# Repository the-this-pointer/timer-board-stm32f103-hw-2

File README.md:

# Timer Board Design Files

This repository contains the KiCAD PCB design files for my <a href="https://github.com/the-this-pointer/timer-board-stm32f103" target="_blank">universal timer board</a>.

There are two PCBs for main board and a panel board to let user set the configuration.

Caution: The PCBs not tested yet!

Main board:

Panel board:

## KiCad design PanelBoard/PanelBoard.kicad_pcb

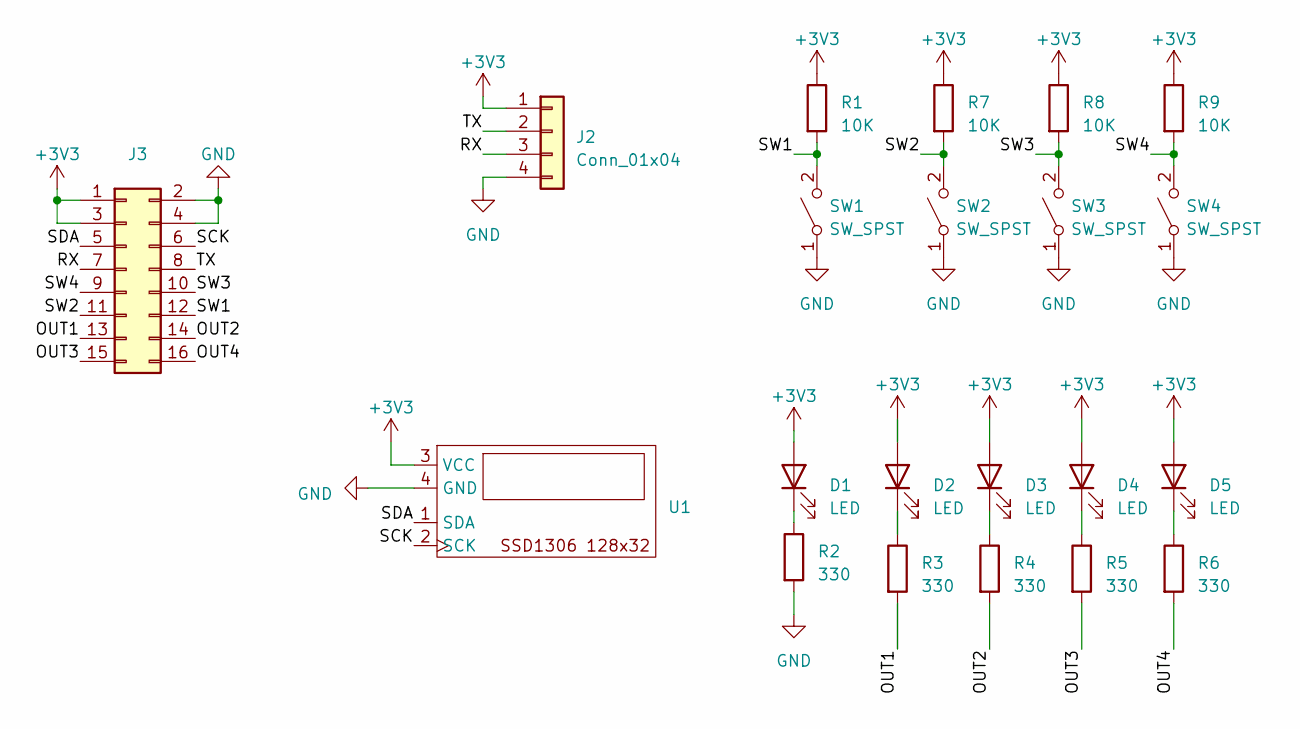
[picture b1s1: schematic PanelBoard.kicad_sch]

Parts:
D1, D2, D3, D4, D5: LED; LED_1206_3216Metric_Pad1.42x1.75mm_HandSolder
J2: Conn_01x04; PinHeader_1x04_P2.54mm_Vertical
J3: Conn_02x08_Odd_Even; PinHeader_2x08_P2.54mm_Horizontal
R1, R7, R8, R9: 10K; R_1206_3216Metric_Pad1.30x1.75mm_HandSolder
R2, R3, R4, R5, R6: 330; R_1206_3216Metric_Pad1.30x1.75mm_HandSolder
SW1, SW2, SW3, SW4: SW_SPST; SW_PUSH_6mm_H13mm
U1: OLED_SSD1306_128x32_0.91

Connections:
+3V3: D1.2 (A), D2.2 (A), D3.2 (A), D4.2 (A), D5.2 (A), J2.1, R1.1, R7.1, R8.1, R9.1, U1.3 (VCC); also elsewhere on the board
/OUT1: R3.2; also elsewhere on the board
/OUT2: R4.2; also elsewhere on the board
/OUT3: R5.2; also elsewhere on the board
/OUT4: R6.2; also elsewhere on the board
/RX: J2.3; also elsewhere on the board
/SCK: U1.2 (SCK); also elsewhere on the board
/SDA: U1.1 (SDA); also elsewhere on the board
/SW1: R1.2, SW1.2 (B); also elsewhere on the board
/SW2: R7.2, SW2.2 (B); also elsewhere on the board
/SW3: R8.2, SW3.2 (B); also elsewhere on the board
/SW4: R9.2, SW4.2 (B); also elsewhere on the board
/TX: J2.2; also elsewhere on the board
GND: J2.4, R2.2, SW1.1 (A), SW2.1 (A), SW3.1 (A), SW4.1 (A), U1.4 (GND); also elsewhere on the board
unnamed: D1.1 (K), R2.1
unnamed: D2.1 (K), R3.1
unnamed: D3.1 (K), R4.1
unnamed: D4.1 (K), R5.1
unnamed: D5.1 (K), R6.1

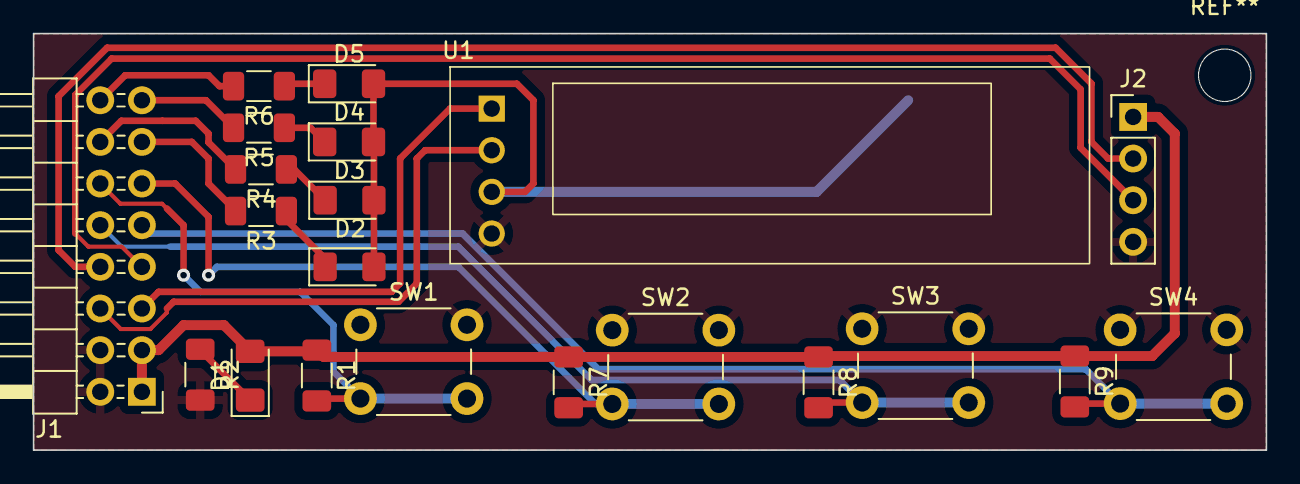
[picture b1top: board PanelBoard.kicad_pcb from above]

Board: 2 copper layers, 75.2 x 25.4 mm, 21 parts (0 on the bottom side), 19 nets.

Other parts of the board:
J1: Conn_02x08_Odd_Even; PinHeader_2x08_P2.54mm_Horizontal

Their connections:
+3V3: J1.1, J1.3; also elsewhere on the board
/OUT1: J1.13; also elsewhere on the board
/OUT2: J1.14; also elsewhere on the board
/OUT3: J1.15; also elsewhere on the board
/OUT4: J1.16; also elsewhere on the board
/RX: J1.7; also elsewhere on the board
/SCK: J1.6; also elsewhere on the board
/SDA: J1.5; also elsewhere on the board
/SW1: J1.12; also elsewhere on the board
/SW2: J1.11; also elsewhere on the board
/SW3: J1.10; also elsewhere on the board
/SW4: J1.9; also elsewhere on the board
/TX: J1.8; also elsewhere on the board
GND: J1.2, J1.4; also elsewhere on the board

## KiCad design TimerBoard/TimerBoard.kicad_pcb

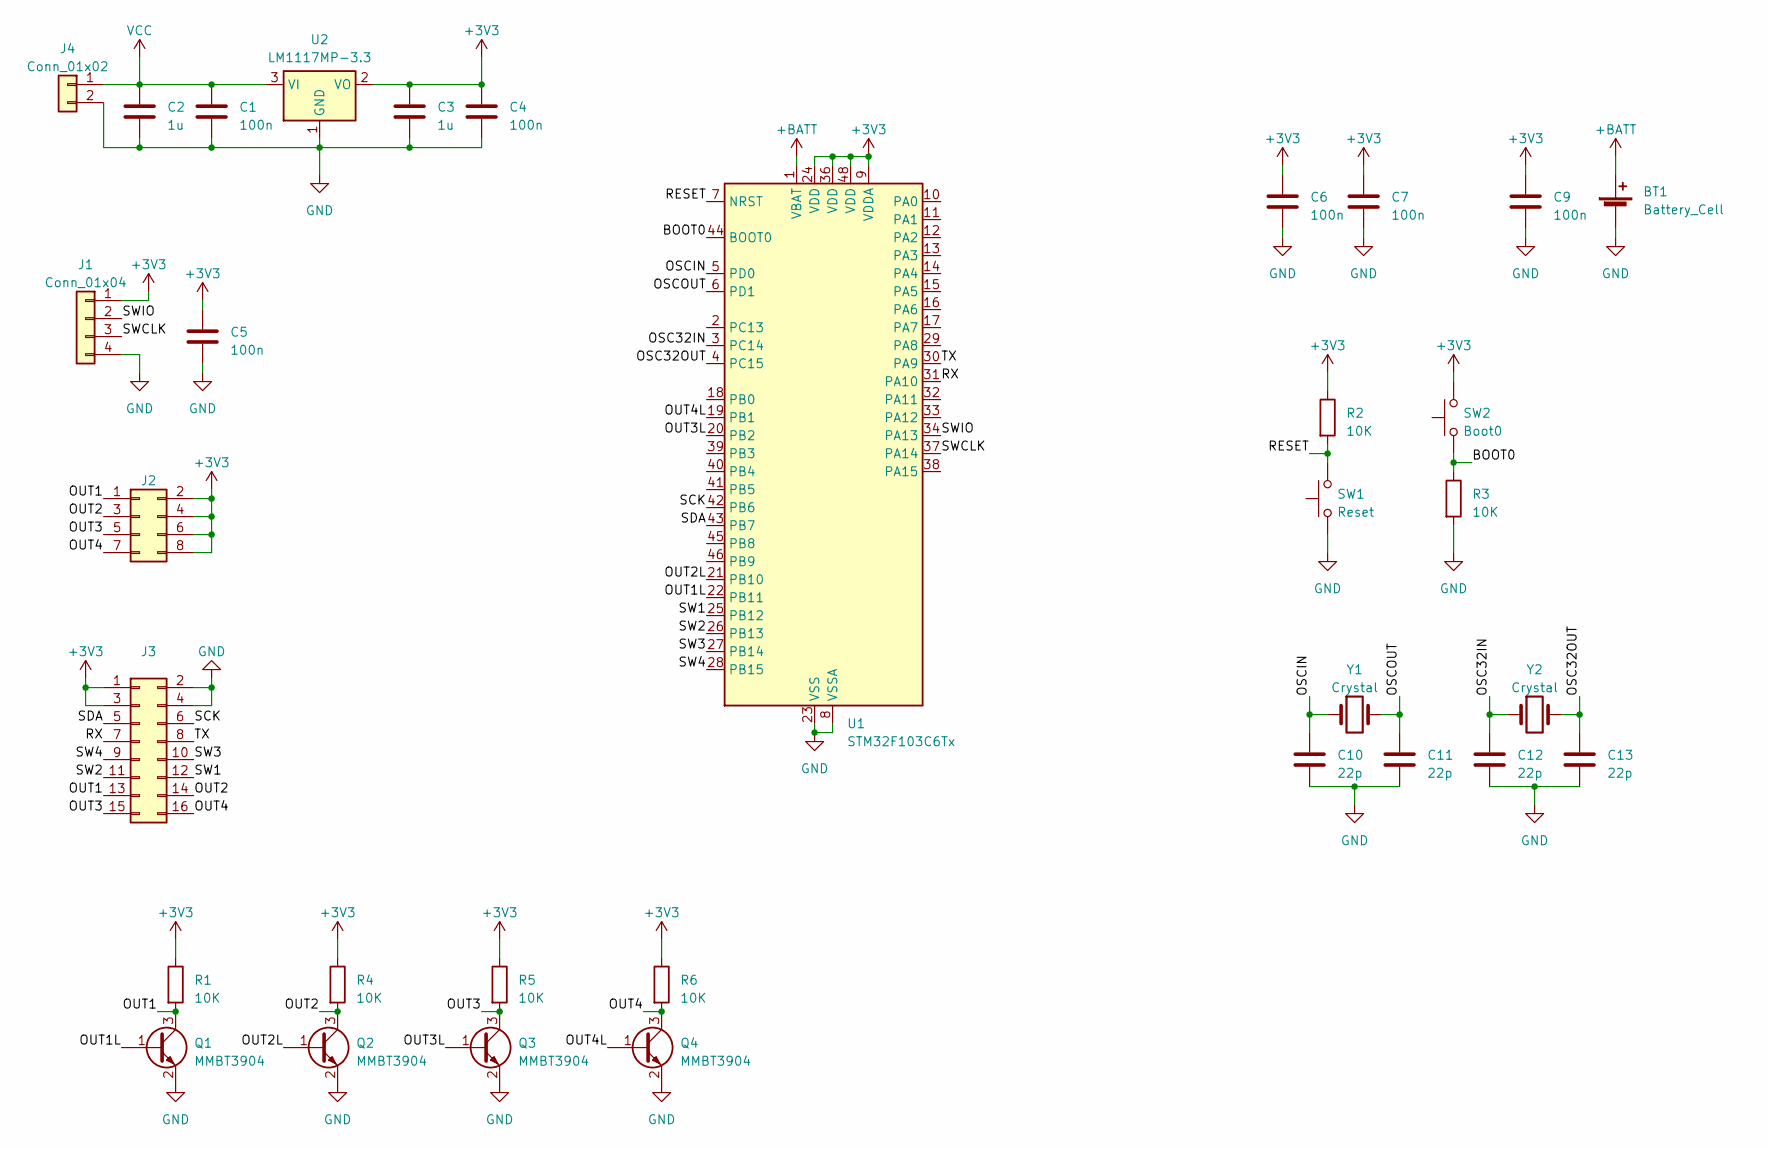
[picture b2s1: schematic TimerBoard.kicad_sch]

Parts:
BT1: Battery_Cell; BatteryHolder_Keystone_104_1x23mm
C1, C4, C5, C6, C7, C9: 100n; C_1206_3216Metric_Pad1.33x1.80mm_HandSolder
C2, C3: 1u; C_1206_3216Metric_Pad1.33x1.80mm_HandSolder
C10, C11, C12, C13: 22p; C_1206_3216Metric_Pad1.33x1.80mm_HandSolder
J1: Conn_01x04; PinHeader_1x04_P2.54mm_Vertical
J2: Conn_02x04_Odd_Even; PinHeader_2x04_P2.54mm_Vertical
J3: Conn_02x08_Odd_Even; PinHeader_2x08_P2.54mm_Horizontal
J4: Conn_01x02; PinHeader_1x02_P2.54mm_Vertical
Q1, Q2, Q3, Q4: MMBT3904; SOT-23
R1, R2, R3, R4, R5, R6: 10K; R_1206_3216Metric_Pad1.30x1.75mm_HandSolder
SW1: Reset; SW_PUSH_6mm
SW2: Boot0; SW_PUSH_6mm
U1: STM32F103C6Tx; LQFP-48_7x7mm_P0.5mm
U2: LM1117MP-3.3; SOT-223-3_TabPin2
Y1: Crystal; Crystal_HC49-U_Vertical
Y2: Crystal; Crystal_C38-LF_D3.0mm_L8.0mm_Horizontal

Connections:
+3V3: C3.1, C4.1, C5.1, C6.1, C7.1, C9.1, J1.1, J2.2, J2.4, J2.6, J2.8, J3.1, J3.3, R1.1, R2.1, R4.1, R5.1, R6.1, SW2.2, U1.9 (VDDA), U1.24 (VDD), U1.36 (VDD), U1.48 (VDD), U2.2 (VO)
+BATT: BT1.1 (+), U1.1 (VBAT)
/BOOT0: R3.1, SW2.1, U1.44 (BOOT0)
/OSC32IN: C12.1, U1.3 (PC14), Y2.1
/OSC32OUT: C13.1, U1.4 (PC15), Y2.2
/OSCIN: C10.1, U1.5 (PD0), Y1.1
/OSCOUT: C11.1, U1.6 (PD1), Y1.2
/OUT1: J2.1, J3.13, Q1.3 (C), R1.2
/OUT1L: Q1.1 (B), U1.22 (PB11)
/OUT2: J2.3, J3.14, Q2.3 (C), R4.2
/OUT2L: Q2.1 (B), U1.21 (PB10)
/OUT3: J2.5, J3.15, Q3.3 (C), R5.2
/OUT3L: Q3.1 (B), U1.20 (PB2)
/OUT4: J2.7, J3.16, Q4.3 (C), R6.2
/OUT4L: Q4.1 (B), U1.19 (PB1)
/RESET: R2.2, SW1.2, U1.7 (NRST)
/RX: J3.7, U1.31 (PA10)
/SCK: J3.6, U1.42 (PB6)
/SDA: J3.5, U1.43 (PB7)
/SW1: J3.12, U1.25 (PB12)
/SW2: J3.11, U1.26 (PB13)
/SW3: J3.10, U1.27 (PB14)
/SW4: J3.9, U1.28 (PB15)
/SWCLK: J1.3, U1.37 (PA14)
/SWIO: J1.2, U1.34 (PA13)
/TX: J3.8, U1.30 (PA9)
GND: BT1.2 (-), C1.2, C2.2, C3.2, C4.2, C5.2, C6.2, C7.2, C9.2, C10.2, C11.2, C12.2, C13.2, J1.4, J3.2, J3.4, J4.2, Q1.2 (E), Q2.2 (E), Q3.2 (E), Q4.2 (E), R3.2, SW1.1, U1.8 (VSSA), U1.23 (VSS), U1.35 (VSS), U1.47 (VSS), U2.1 (GND)
VCC: C1.1, C2.1, J4.1, U2.3 (VI)

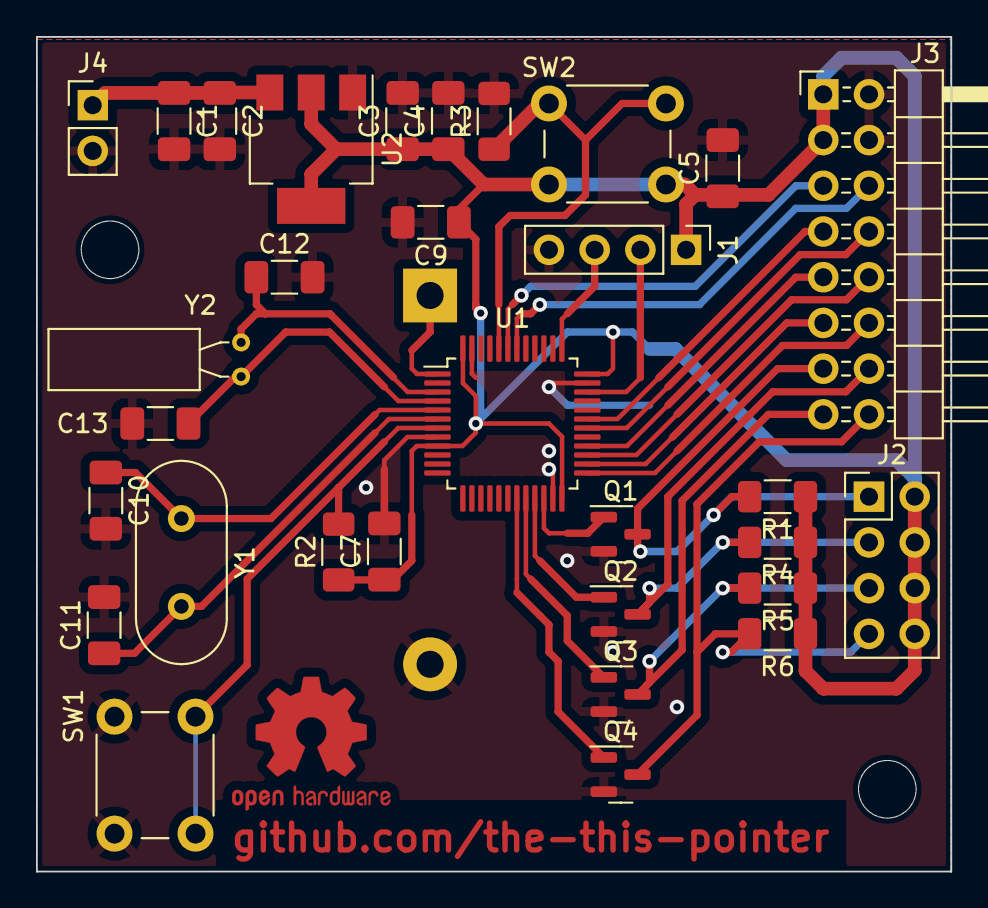
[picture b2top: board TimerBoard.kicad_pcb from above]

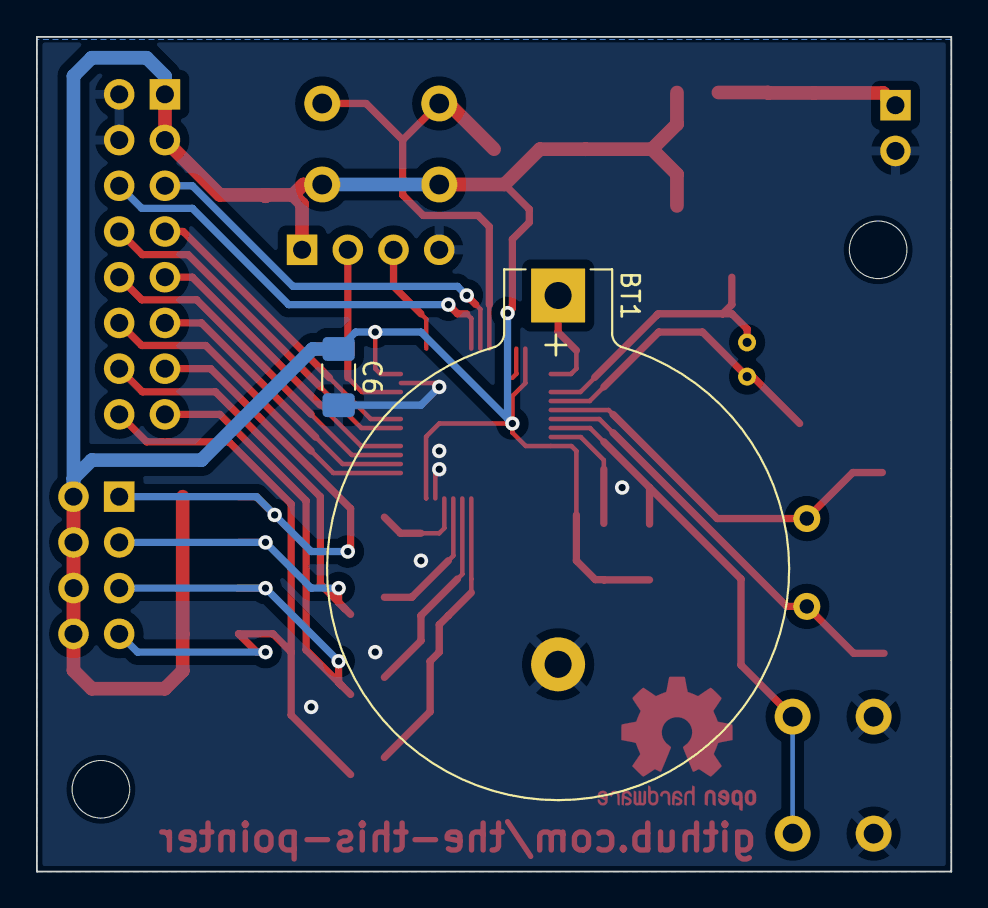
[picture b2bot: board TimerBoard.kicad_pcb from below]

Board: 2 copper layers, 50.8 x 46.4 mm, 33 parts (2 on the bottom side), 28 nets.

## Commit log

2023-03-23 panel pcb project created
2023-03-24 timer board added
2023-03-25 panel board pcb designed
2023-05-04 readme updated
